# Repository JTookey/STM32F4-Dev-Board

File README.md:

# STM32F4 Dev Board
 Simple STM32F4 based board for electronics projects

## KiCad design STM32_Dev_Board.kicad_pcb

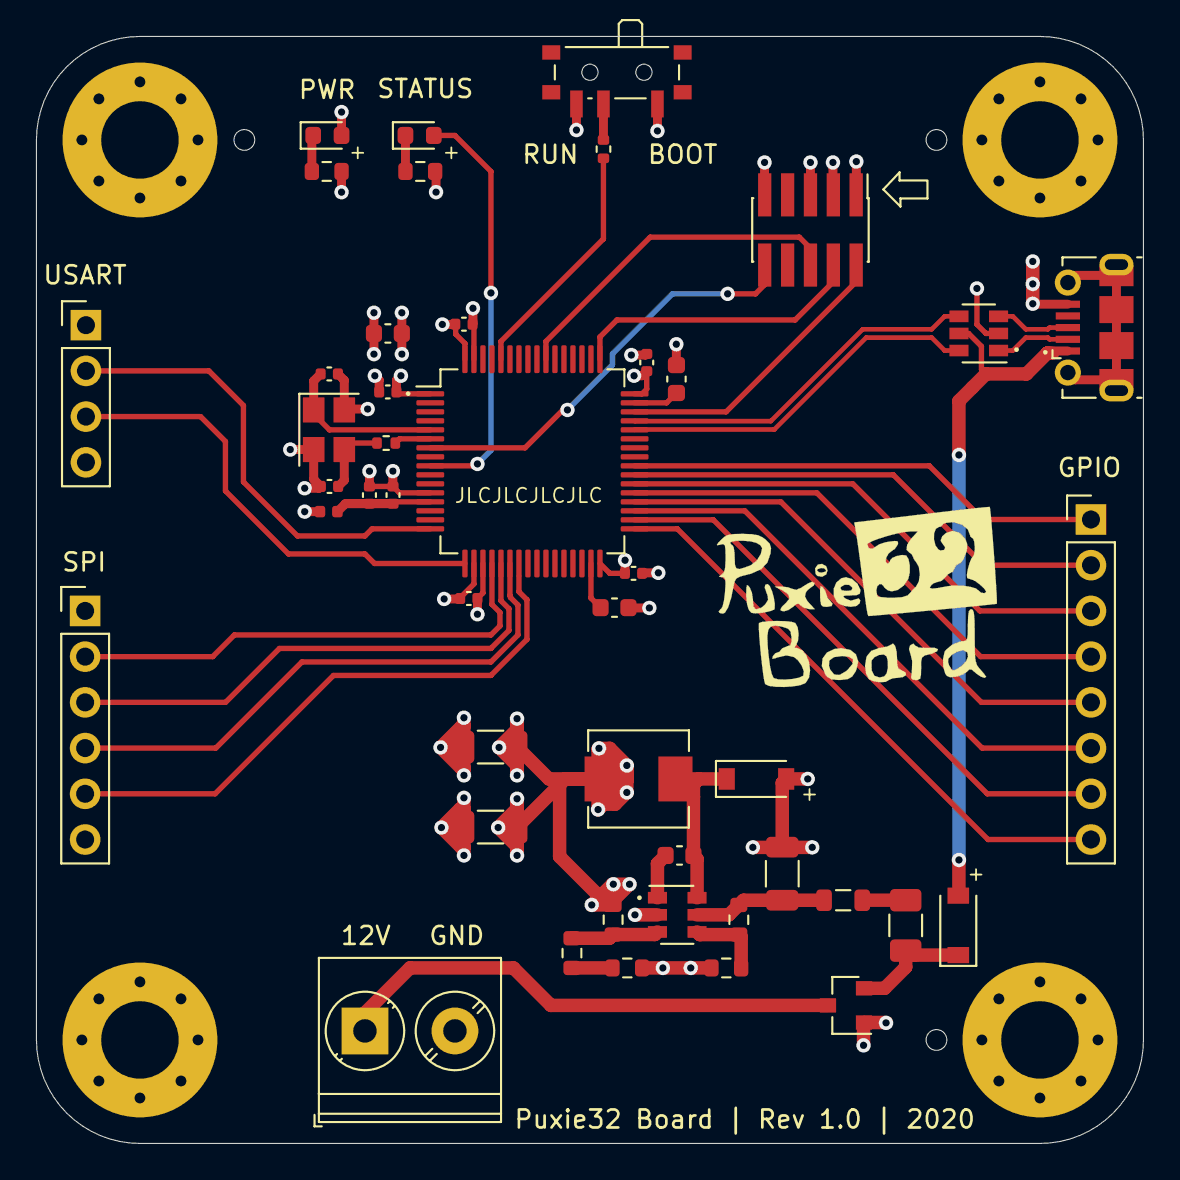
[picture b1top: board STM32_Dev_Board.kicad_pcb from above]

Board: 4 copper layers, 61.5 x 61.5 mm, 49 parts (0 on the bottom side), 45 nets.

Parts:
C1, C2, C3: 10u; C_1206_3216Metric
C4: 10n; C_0603_1608Metric
C5: 4u7; C_0603_1608Metric
C6, C7, C8, C9, C10: 100n; C_0402_1005Metric
C11: 1u; C_0402_1005Metric
C12: 10n; C_0402_1005Metric
C13, C14: 2u2; C_0603_1608Metric
C15, C16: 12p; C_0402_1005Metric
D1: BLUE; LED_0603_1608Metric
D2, D3: B5819W; D_SOD-123
D4: RED; LED_0603_1608Metric
F1: 250mA; Fuse_1206_3216Metric
FB1: 600 @ 600MHz; L_0805_2012Metric
H1, H2, H3, H4: MountingHole_Pad; MountingHole_4.3mm_M4_Pad_Via
J1: USB_B_Micro; USB_Micro-B_Molex-105017-0001
J2: Power; TerminalBlock_Phoenix_PT-1,5-2-5.0-H_1x02_P5.00mm_Horizontal
J3: USART; PinHeader_1x04_P2.54mm_Vertical
J4: SWD; PinHeader_2x05_P1.27mm_Vertical_SMD
J5: SPI; PinHeader_1x06_P2.54mm_Vertical
J6: GPIO; PinHeader_1x08_P2.54mm_Vertical
L1: 39n; L_0402_1005Metric
L2: 10u; L_Sunlord_MWSA0518_5.4x5.2mm
Q1: AO3401A; SOT-23
R1: 100k; R_0603_1608Metric
R2: 68k; R_0603_1608Metric
R3: 47k; R_0603_1608Metric
R4: 15k; R_0603_1608Metric
R5: 270; R_0603_1608Metric
R6: 1k; R_0603_1608Metric
R7: 10k; R_0402_1005Metric
R8: 47; R_0402_1005Metric
R9: 1k5; R_0603_1608Metric
SW1: SW_SPDT; SW_SPDT_PCM12
U1: STM32F405RGT6; LQFP-64_10x10mm_P0.5mm
U2: MP2359DJ-LF-Z; SOT-23-6
U3: USBLC6-2SC6; SOT-23-6
Y1: 16MHz; Crystal_SMD_3225-4Pin_3.2x2.5mm

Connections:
+3.3VA: C11.1, C12.1, L1.2, U1.13
+3V3: C2.1, C3.1, C5.1, C6.1, C7.1, C8.1, C9.1, C10.1, D4.2, J3.1, J4.1, J5.1, L1.1, L2.2, R3.2, SW1.1, U1.1, U1.19, U1.32, U1.48, U1.64
+5V: D2.2, J1.1, U3.5
+12V: J2.1, Q1.3
BOOT0: R7.2, U1.60
BUCK_BST: C4.1, U2.1
BUCK_EN: R1.1, R2.2, U2.4
BUCK_FB: R3.1, R4.2, U2.3
BUCK_IN: C1.1, FB1.1, R1.2, U2.5
BUCK_SW: C4.2, D3.1, L2.1, U2.6
GND: C1.2, C2.2, C3.2, C5.2, C6.2, C7.2, C8.2, C9.2, C10.2, C11.2, C12.2, C13.2, C14.2, C15.2, C16.2, D3.2, H1.1, H2.1, H3.1, H4.1, J1.5, J2.2, J3.4, J4.3, J4.5, J4.9, J5.6, Q1.1, R2.1, R5.1, R6.1, R9.1, SW1.3, U1.12, U1.18, U1.63, U2.2, U3.2, Y1.2, Y1.4
GPIO_0: J6.1, U1.40
GPIO_1: J6.2, U1.39
GPIO_2: J6.3, U1.38
GPIO_3: J6.4, U1.37
GPIO_4: J6.5, U1.36
GPIO_5: J6.6, U1.35
GPIO_6: J6.7, U1.34
GPIO_7: J6.8, U1.33
HS_CLK_IN: C15.1, U1.5, Y1.1
HS_CLK_OUT: R8.1, U1.6
NRST: J4.10, U1.7
unnamed: C13.1, U1.31
unnamed: C14.1, U1.47
unnamed: C16.1, R8.2, Y1.3
unnamed: D1.1, R9.2
unnamed: D2.1, F1.2, Q1.2
unnamed: D4.1, R6.2
unnamed: F1.1, FB1.2
unnamed: R4.1, R5.2
unnamed: R7.1, SW1.2
SPI1_CS: J5.2, U1.20
SPI1_MISO: J5.4, U1.22
SPI1_MOSI: J5.5, U1.23
SPI1_SCK: J5.3, U1.21
STATUS_LED: D1.2, U1.9
SWCLK: J4.4, U1.49
SWDIO: J4.2, U1.46
SWO: J4.6, U1.55
USART2_TX: J3.2, U1.16
USART4_RX: J3.3, U1.17
USB_Conn_D+: J1.3, U3.3
USB_Conn_D-: J1.2, U3.1
USB_D+: U1.45, U3.4
USB_D-: U1.44, U3.6

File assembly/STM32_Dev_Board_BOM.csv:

Comment,Designator,Footprint,LCSC
"10u","C1,C2,C3","Capacitor_SMD:C_1206_3216Metric","C13585"
"1u","C11","Capacitor_SMD:C_0402_1005Metric","C52923"
"10n","C12","Capacitor_SMD:C_0402_1005Metric","C15195"
"2u2","C13,C14","Capacitor_SMD:C_0603_1608Metric","C23630"
"12p","C15,C16","Capacitor_SMD:C_0402_1005Metric","C1547"
"10n","C4","Capacitor_SMD:C_0603_1608Metric","C57112"
"4u7","C5","Capacitor_SMD:C_0603_1608Metric","C19666"
"100n","C6,C7,C8,C9,C10","Capacitor_SMD:C_0402_1005Metric","C1525"
"BLUE","D1","LED_SMD:LED_0603_1608Metric","C72041"
"B5819W","D2,D3","Diode_SMD:D_SOD-123","C8598"
"RED","D4","LED_SMD:LED_0603_1608Metric","C2286"
"250mA","F1","Fuse:Fuse_1206_3216Metric","C369159"
"600 @ 600MHz","FB1","Inductor_SMD:L_0805_2012Metric","C1017"
"MountingHole_Pad","H1,H2,H3,H4","MountingHole:MountingHole_4.3mm_M4_Pad_Via",""
"USB_B_Micro","J1","Connector_USB:USB_Micro-B_Molex-105017-0001",""
"Power","J2","TerminalBlock_Phoenix:TerminalBlock_Phoenix_PT-1,5-2-5.0-H_1x02_P5.00mm_Horizontal",""
"USART","J3","Connector_PinHeader_2.54mm:PinHeader_1x04_P2.54mm_Vertical",""
"SWD","J4","Connector_PinHeader_1.27mm:PinHeader_2x05_P1.27mm_Vertical_SMD",""
"SPI","J5","Connector_PinHeader_2.54mm:PinHeader_1x06_P2.54mm_Vertical",""
"GPIO","J6","Connector_PinHeader_2.54mm:PinHeader_1x08_P2.54mm_Vertical",""
"39n","L1","Inductor_SMD:L_0402_1005Metric","C26443"
"10u","L2","Inductor_SMD:L_Sunlord_MWSA0518_5.4x5.2mm","C408412"
"AO3401A","Q1","Package_TO_SOT_SMD:SOT-23","C15127"
"100k","R1","Resistor_SMD:R_0603_1608Metric","C25803"
"68k","R2","Resistor_SMD:R_0603_1608Metric","C23231"
"47k","R3","Resistor_SMD:R_0603_1608Metric","C25819"
"15k","R4","Resistor_SMD:R_0603_1608Metric","C22809"
"270","R5","Resistor_SMD:R_0603_1608Metric","C22966"
"1k","R6","Resistor_SMD:R_0603_1608Metric","C21190"
"10k","R7","Resistor_SMD:R_0402_1005Metric","C25744"
"47","R8","Resistor_SMD:R_0402_1005Metric","C25118"
"1k5","R9","Resistor_SMD:R_0603_1608Metric","C22843"
"SW_SPDT","SW1","Button_Switch_SMD:SW_SPDT_PCM12",""
"STM32F405RGT6","U1","Package_QFP:LQFP-64_10x10mm_P0.5mm","C15742"
"MP2359DJ-LF-Z","U2","Package_TO_SOT_SMD:SOT-23-6","C14259"
"USBLC6-2SC6","U3","Package_TO_SOT_SMD:SOT-23-6","C7519"
"16MHz","Y1","Crystal:Crystal_SMD_3225-4Pin_3.2x2.5mm","C13738"

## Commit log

2020-12-15 Initial Version
    Revision 1.0 of the board
